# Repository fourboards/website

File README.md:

# fourboards
-----

Website based on the *Junior* theme designed and developed by [@jonobelotti_IO](https://twitter.com/jonobelotti_IO).

It is designed for [Jekyll](http://jekyllrb.com), the static site generator.

### Running 

`bundle exec jekyll serve`

## Credit

* [Pixyll theme](https://github.com/johnotander/pixyll) was used as a base for development of this theme.
* [Junior.IO's](http://www.junior.io/) website design served as inspiration for this theme's look.

## License

Open sourced under the [MIT license](LICENSE).

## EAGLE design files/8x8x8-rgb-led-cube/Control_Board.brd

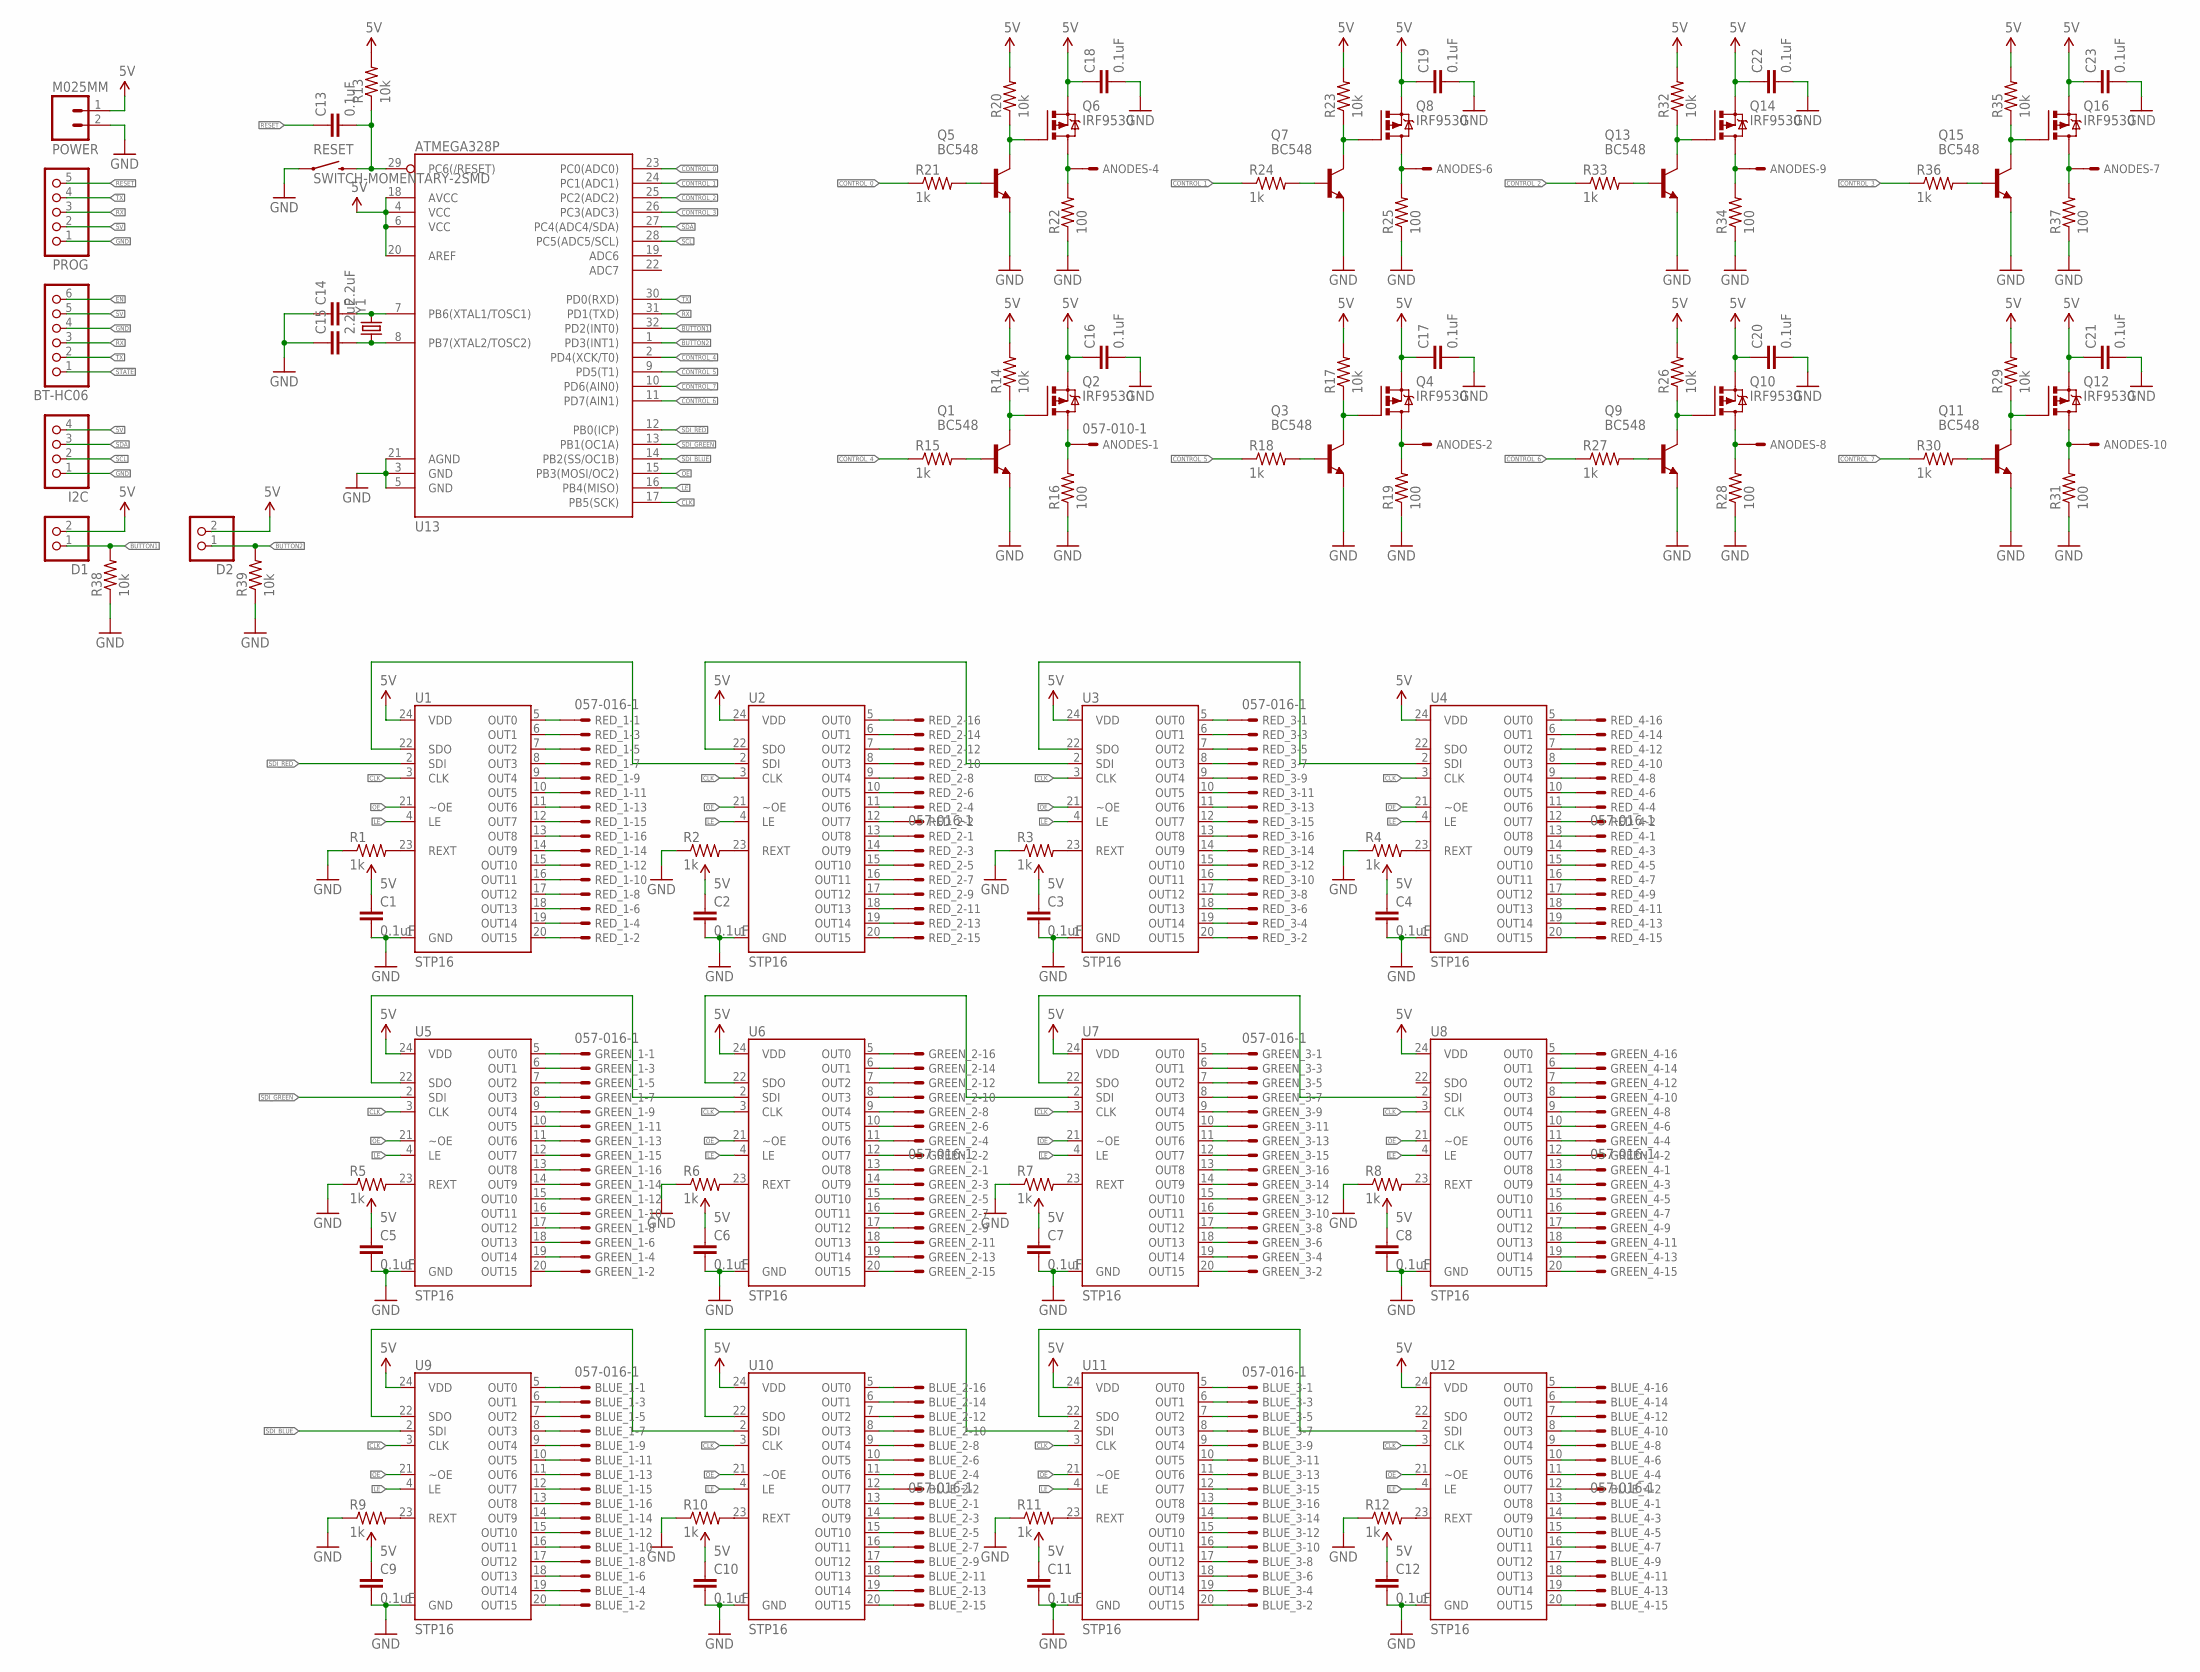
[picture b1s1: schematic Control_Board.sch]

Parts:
ANODES: 057-010-1
BLUE_1, BLUE_2, BLUE_3, BLUE_4: 057-016-1
BT-HC06: PINHD-1X6/90; 1X06/90
C1, C2, C3, C4, C5, C6, C7, C8, C9, C10, C11, C12, C13, C16, C17, C18, C19, C20, C21, C22, C23: 0.1uF; 0603-CAP
C14, C15: 2.2uF; 0603-CAP
D1, D2: PINHD-1X2/90; 1X02/90
GREEN_1, GREEN_2, GREEN_3, GREEN_4: 057-016-1
I2C: PINHD-1X4/90; 1X04/90
POWER: M025MM; SCREWTERMINAL-5MM-2
PROG: PINHD-1X5/90; 1X05/90
Q1, Q3, Q5, Q7, Q9, Q11, Q13, Q15: BC548; TO92-EBC
Q2, Q4, Q6, Q8, Q10, Q12, Q14, Q16: IRF9530; TO220BV
R1, R2, R3, R4, R5, R6, R7, R8, R9, R10, R11, R12, R15, R18, R21, R24, R27, R30, R33, R36: 1k; 0603-RES
R13, R14, R17, R20, R23, R26, R29, R32, R35, R38, R39: 10k; 0603-RES
R16, R19, R22, R25, R28, R31, R34, R37: 100; 0603-RES
RED_1, RED_2, RED_3, RED_4: 057-016-1
RESET: SWITCH-MOMENTARY-2SMD; TACTILE_SWITCH_SMD
U1, U2, U3, U4, U5, U6, U7, U8, U9, U10, U11, U12: STP16; TSSOP-24
U13: ATMEGA328P; TQFP32-08
Y1: CRYSTALHC49UV; HC49U-V

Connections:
5V: BT-HC06.5, C1.1, C2.1, C3.1, C4.1, C5.1, C6.1, C7.1, C8.1, C9.1, C10.1, C11.1, C12.1, C16.1, C17.1, C18.1, C19.1, C20.1, C21.1, C22.1, C23.1, D1.2, D2.2, I2C.4, POWER.1, PROG.2, Q2.S, Q4.S, Q6.S, Q8.S, Q10.S, Q12.S, Q14.S, Q16.S, R13.2, R14.2, R17.2, R20.2, R23.2, R26.2, R29.2, R32.2, R35.2, U1.24 (VDD), U2.24 (VDD), U3.24 (VDD), U4.24 (VDD), U5.24 (VDD), U6.24 (VDD), U7.24 (VDD), U8.24 (VDD), U9.24 (VDD), U10.24 (VDD), U11.24 (VDD), U12.24 (VDD), U13.6 (VCC), U13.18 (AVCC), U13.20 (AREF)
BUTTON1: D1.1, R38.2, U13.32 (PD2(INT0))
BUTTON2: D2.1, R39.2, U13.1 (PD3(INT1))
CLK: U1.3 (CLK), U2.3 (CLK), U3.3 (CLK), U4.3 (CLK), U5.3 (CLK), U6.3 (CLK), U7.3 (CLK), U8.3 (CLK), U9.3 (CLK), U10.3 (CLK), U11.3 (CLK), U12.3 (CLK), U13.17 (PB5(SCK))
CONTROL_0: R21.1, U13.23 (PC0(ADC0))
CONTROL_1: R24.1, U13.24 (PC1(ADC1))
CONTROL_2: R33.1, U13.25 (PC2(ADC2))
CONTROL_3: R36.1, U13.26 (PC3(ADC3))
CONTROL_4: R15.1, U13.2 (PD4(XCK/T0))
CONTROL_5: R18.1, U13.9 (PD5(T1))
CONTROL_6: R27.1, U13.11 (PD7(AIN1))
CONTROL_7: R30.1, U13.10 (PD6(AIN0))
EN: BT-HC06.6
GND: BT-HC06.4, C1.2, C2.2, C3.2, C4.2, C5.2, C6.2, C7.2, C8.2, C9.2, C10.2, C11.2, C12.2, C14.1, C15.1, C16.2, C17.2, C18.2, C19.2, C20.2, C21.2, C22.2, C23.2, I2C.1, POWER.2, PROG.1, Q1.E, Q3.E, Q5.E, Q7.E, Q9.E, Q11.E, Q13.E, Q15.E, R1.1, R2.1, R3.1, R4.1, R5.1, R6.1, R7.1, R8.1, R9.1, R10.1, R11.1, R12.1, R16.1, R19.1, R22.1, R25.1, R28.1, R31.1, R34.1, R37.1, R38.1, R39.1, RESET.1, U1.1 (GND), U2.1 (GND), U3.1 (GND), U4.1 (GND), U5.1 (GND), U6.1 (GND), U7.1 (GND), U8.1 (GND), U9.1 (GND), U10.1 (GND), U11.1 (GND), U12.1 (GND), U13.5 (GND), U13.21 (AGND)
LE: U1.4 (LE), U2.4 (LE), U3.4 (LE), U4.4 (LE), U5.4 (LE), U6.4 (LE), U7.4 (LE), U8.4 (LE), U9.4 (LE), U10.4 (LE), U11.4 (LE), U12.4 (LE), U13.16 (PB4(MISO))
LEVEL_0: ANODES.4, Q6.D, R22.2
LEVEL_1: ANODES.6, Q8.D, R25.2
LEVEL_2: ANODES.9, Q14.D, R34.2
LEVEL_3: ANODES.7, Q16.D, R37.2
LEVEL_4: ANODES.1, Q2.D, R16.2
LEVEL_5: ANODES.2, Q4.D, R19.2
LEVEL_6: ANODES.8, Q10.D, R28.2
LEVEL_7: ANODES.10, Q12.D, R31.2
unnamed: R1.2, U1.23 (REXT)
unnamed: RED_1.16, U1.13 (OUT8)
unnamed: RED_1.14, U1.14 (OUT9)
unnamed: RED_1.12, U1.15 (OUT10)
unnamed: RED_1.10, U1.16 (OUT11)
unnamed: RED_1.8, U1.17 (OUT12)
unnamed: RED_1.6, U1.18 (OUT13)
unnamed: RED_1.4, U1.19 (OUT14)
unnamed: RED_1.2, U1.20 (OUT15)
unnamed: RED_1.15, U1.12 (OUT7)
unnamed: RED_1.13, U1.11 (OUT6)
unnamed: RED_1.11, U1.10 (OUT5)
unnamed: RED_1.9, U1.9 (OUT4)
unnamed: RED_1.7, U1.8 (OUT3)
unnamed: RED_1.5, U1.7 (OUT2)
unnamed: RED_1.3, U1.6 (OUT1)
unnamed: RED_1.1, U1.5 (OUT0)
unnamed: R2.2, U2.23 (REXT)
unnamed: RED_2.2, U2.12 (OUT7)
unnamed: RED_2.4, U2.11 (OUT6)
unnamed: RED_2.6, U2.10 (OUT5)
unnamed: RED_2.8, U2.9 (OUT4)
unnamed: RED_2.10, U2.8 (OUT3)
unnamed: RED_2.12, U2.7 (OUT2)
unnamed: RED_2.14, U2.6 (OUT1)
unnamed: RED_2.16, U2.5 (OUT0)
unnamed: RED_2.1, U2.13 (OUT8)
unnamed: RED_2.3, U2.14 (OUT9)
unnamed: RED_2.5, U2.15 (OUT10)
unnamed: RED_2.7, U2.16 (OUT11)
unnamed: RED_2.9, U2.17 (OUT12)
unnamed: RED_2.11, U2.18 (OUT13)
unnamed: RED_2.13, U2.19 (OUT14)
unnamed: RED_2.15, U2.20 (OUT15)
unnamed: R3.2, U3.23 (REXT)
unnamed: RED_3.1, U3.5 (OUT0)
unnamed: RED_3.2, U3.20 (OUT15)
unnamed: RED_3.3, U3.6 (OUT1)
unnamed: RED_3.4, U3.19 (OUT14)
unnamed: RED_3.5, U3.7 (OUT2)
unnamed: RED_3.6, U3.18 (OUT13)
unnamed: RED_3.7, U3.8 (OUT3)
unnamed: RED_3.8, U3.17 (OUT12)
unnamed: RED_3.9, U3.9 (OUT4)
unnamed: RED_3.10, U3.16 (OUT11)
unnamed: RED_3.11, U3.10 (OUT5)
unnamed: RED_3.12, U3.15 (OUT10)
unnamed: RED_3.13, U3.11 (OUT6)
unnamed: RED_3.14, U3.14 (OUT9)
unnamed: RED_3.15, U3.12 (OUT7)
unnamed: RED_3.16, U3.13 (OUT8)
unnamed: R4.2, U4.23 (REXT)
unnamed: RED_4.1, U4.13 (OUT8)
unnamed: RED_4.2, U4.12 (OUT7)
unnamed: RED_4.3, U4.14 (OUT9)
unnamed: RED_4.4, U4.11 (OUT6)
unnamed: RED_4.5, U4.15 (OUT10)
unnamed: RED_4.6, U4.10 (OUT5)
unnamed: RED_4.7, U4.16 (OUT11)
unnamed: RED_4.8, U4.9 (OUT4)
unnamed: RED_4.9, U4.17 (OUT12)
unnamed: RED_4.10, U4.8 (OUT3)
unnamed: RED_4.11, U4.18 (OUT13)
unnamed: RED_4.12, U4.7 (OUT2)
unnamed: RED_4.13, U4.19 (OUT14)
unnamed: RED_4.14, U4.6 (OUT1)
unnamed: RED_4.15, U4.20 (OUT15)
unnamed: RED_4.16, U4.5 (OUT0)
unnamed: U1.22 (SDO), U2.2 (SDI)
unnamed: U2.22 (SDO), U3.2 (SDI)
unnamed: U3.22 (SDO), U4.2 (SDI)
unnamed: R5.2, U5.23 (REXT)
unnamed: R6.2, U6.23 (REXT)
unnamed: R7.2, U7.23 (REXT)
unnamed: R8.2, U8.23 (REXT)
unnamed: U5.22 (SDO), U6.2 (SDI)
unnamed: U6.22 (SDO), U7.2 (SDI)
unnamed: U7.22 (SDO), U8.2 (SDI)
unnamed: GREEN_1.16, U5.13 (OUT8)
unnamed: GREEN_1.14, U5.14 (OUT9)
unnamed: GREEN_1.12, U5.15 (OUT10)
unnamed: GREEN_1.10, U5.16 (OUT11)
unnamed: GREEN_1.8, U5.17 (OUT12)
unnamed: GREEN_1.6, U5.18 (OUT13)
unnamed: GREEN_1.4, U5.19 (OUT14)
unnamed: GREEN_1.2, U5.20 (OUT15)
unnamed: GREEN_1.15, U5.12 (OUT7)
unnamed: GREEN_1.13, U5.11 (OUT6)
unnamed: GREEN_1.11, U5.10 (OUT5)
unnamed: GREEN_1.9, U5.9 (OUT4)
unnamed: GREEN_1.7, U5.8 (OUT3)
unnamed: GREEN_1.5, U5.7 (OUT2)
unnamed: GREEN_1.3, U5.6 (OUT1)
unnamed: GREEN_1.1, U5.5 (OUT0)
unnamed: GREEN_3.1, U7.5 (OUT0)
unnamed: GREEN_3.2, U7.20 (OUT15)
unnamed: GREEN_3.3, U7.6 (OUT1)
unnamed: GREEN_3.4, U7.19 (OUT14)
unnamed: GREEN_3.5, U7.7 (OUT2)
unnamed: GREEN_3.6, U7.18 (OUT13)
unnamed: GREEN_3.7, U7.8 (OUT3)
unnamed: GREEN_3.8, U7.17 (OUT12)
unnamed: GREEN_3.9, U7.9 (OUT4)
unnamed: GREEN_3.10, U7.16 (OUT11)
unnamed: GREEN_3.11, U7.10 (OUT5)
unnamed: GREEN_3.12, U7.15 (OUT10)
unnamed: GREEN_3.13, U7.11 (OUT6)
unnamed: GREEN_3.14, U7.14 (OUT9)
unnamed: GREEN_3.15, U7.12 (OUT7)
unnamed: GREEN_3.16, U7.13 (OUT8)
unnamed: GREEN_2.2, U6.12 (OUT7)
unnamed: GREEN_2.4, U6.11 (OUT6)
unnamed: GREEN_2.6, U6.10 (OUT5)
unnamed: GREEN_2.8, U6.9 (OUT4)
unnamed: GREEN_2.10, U6.8 (OUT3)
unnamed: GREEN_2.12, U6.7 (OUT2)
unnamed: GREEN_2.14, U6.6 (OUT1)
unnamed: GREEN_2.16, U6.5 (OUT0)
unnamed: GREEN_2.1, U6.13 (OUT8)
unnamed: GREEN_2.3, U6.14 (OUT9)
unnamed: GREEN_2.5, U6.15 (OUT10)
unnamed: GREEN_2.7, U6.16 (OUT11)
unnamed: GREEN_2.9, U6.17 (OUT12)
unnamed: GREEN_2.11, U6.18 (OUT13)
unnamed: GREEN_2.13, U6.19 (OUT14)
unnamed: GREEN_2.15, U6.20 (OUT15)
unnamed: GREEN_4.1, U8.13 (OUT8)
unnamed: GREEN_4.2, U8.12 (OUT7)
unnamed: GREEN_4.3, U8.14 (OUT9)
unnamed: GREEN_4.4, U8.11 (OUT6)
unnamed: GREEN_4.5, U8.15 (OUT10)
unnamed: GREEN_4.6, U8.10 (OUT5)
unnamed: GREEN_4.7, U8.16 (OUT11)
unnamed: GREEN_4.8, U8.9 (OUT4)
unnamed: GREEN_4.9, U8.17 (OUT12)
unnamed: GREEN_4.10, U8.8 (OUT3)
unnamed: GREEN_4.11, U8.18 (OUT13)
unnamed: GREEN_4.12, U8.7 (OUT2)
unnamed: GREEN_4.13, U8.19 (OUT14)
unnamed: GREEN_4.14, U8.6 (OUT1)
unnamed: GREEN_4.15, U8.20 (OUT15)
unnamed: GREEN_4.16, U8.5 (OUT0)
unnamed: R9.2, U9.23 (REXT)
unnamed: R10.2, U10.23 (REXT)
unnamed: R11.2, U11.23 (REXT)
unnamed: R12.2, U12.23 (REXT)
unnamed: U9.22 (SDO), U10.2 (SDI)
unnamed: U10.22 (SDO), U11.2 (SDI)
unnamed: U11.22 (SDO), U12.2 (SDI)
unnamed: BLUE_1.16, U9.13 (OUT8)
unnamed: BLUE_1.14, U9.14 (OUT9)
unnamed: BLUE_1.12, U9.15 (OUT10)
unnamed: BLUE_1.10, U9.16 (OUT11)
unnamed: BLUE_1.8, U9.17 (OUT12)
unnamed: BLUE_1.6, U9.18 (OUT13)
unnamed: BLUE_1.4, U9.19 (OUT14)
unnamed: BLUE_1.2, U9.20 (OUT15)
unnamed: BLUE_1.15, U9.12 (OUT7)
unnamed: BLUE_1.13, U9.11 (OUT6)
unnamed: BLUE_1.11, U9.10 (OUT5)
unnamed: BLUE_1.9, U9.9 (OUT4)
unnamed: BLUE_1.7, U9.8 (OUT3)
unnamed: BLUE_1.5, U9.7 (OUT2)
unnamed: BLUE_1.3, U9.6 (OUT1)
unnamed: BLUE_1.1, U9.5 (OUT0)
unnamed: BLUE_3.1, U11.5 (OUT0)
unnamed: BLUE_3.2, U11.20 (OUT15)
unnamed: BLUE_3.3, U11.6 (OUT1)
unnamed: BLUE_3.4, U11.19 (OUT14)
unnamed: BLUE_3.5, U11.7 (OUT2)
unnamed: BLUE_3.6, U11.18 (OUT13)
unnamed: BLUE_3.7, U11.8 (OUT3)
unnamed: BLUE_3.8, U11.17 (OUT12)
unnamed: BLUE_3.9, U11.9 (OUT4)
unnamed: BLUE_3.10, U11.16 (OUT11)
unnamed: BLUE_3.11, U11.10 (OUT5)
unnamed: BLUE_3.12, U11.15 (OUT10)
unnamed: BLUE_3.13, U11.11 (OUT6)
unnamed: BLUE_3.14, U11.14 (OUT9)
unnamed: BLUE_3.15, U11.12 (OUT7)
unnamed: BLUE_3.16, U11.13 (OUT8)
unnamed: BLUE_2.2, U10.12 (OUT7)
unnamed: BLUE_2.4, U10.11 (OUT6)
unnamed: BLUE_2.6, U10.10 (OUT5)
unnamed: BLUE_2.8, U10.9 (OUT4)
unnamed: BLUE_2.10, U10.8 (OUT3)
unnamed: BLUE_2.12, U10.7 (OUT2)
unnamed: BLUE_2.14, U10.6 (OUT1)
unnamed: BLUE_2.16, U10.5 (OUT0)
unnamed: BLUE_2.1, U10.13 (OUT8)
unnamed: BLUE_2.3, U10.14 (OUT9)
unnamed: BLUE_2.5, U10.15 (OUT10)
unnamed: BLUE_2.7, U10.16 (OUT11)
unnamed: BLUE_2.9, U10.17 (OUT12)
unnamed: BLUE_2.11, U10.18 (OUT13)
unnamed: BLUE_2.13, U10.19 (OUT14)
unnamed: BLUE_2.15, U10.20 (OUT15)
unnamed: BLUE_4.1, U12.13 (OUT8)
unnamed: BLUE_4.2, U12.12 (OUT7)
unnamed: BLUE_4.3, U12.14 (OUT9)
unnamed: BLUE_4.4, U12.11 (OUT6)
unnamed: BLUE_4.5, U12.15 (OUT10)
unnamed: BLUE_4.6, U12.10 (OUT5)
unnamed: BLUE_4.7, U12.16 (OUT11)
unnamed: BLUE_4.8, U12.9 (OUT4)
unnamed: BLUE_4.9, U12.17 (OUT12)
unnamed: BLUE_4.10, U12.8 (OUT3)
unnamed: BLUE_4.11, U12.18 (OUT13)
unnamed: BLUE_4.12, U12.7 (OUT2)
unnamed: BLUE_4.13, U12.19 (OUT14)
unnamed: BLUE_4.14, U12.6 (OUT1)
unnamed: BLUE_4.15, U12.20 (OUT15)
unnamed: BLUE_4.16, U12.5 (OUT0)
unnamed: C13.2, R13.1, RESET.3 (2), U13.29 (PC6(/RESET))
unnamed: Q1.C, Q2.G, R14.1
unnamed: C14.2, U13.7 (PB6(XTAL1/TOSC1)), Y1.2
unnamed: C15.2, U13.8 (PB7(XTAL2/TOSC2)), Y1.1
unnamed: Q1.B, R15.2
unnamed: Q3.C, Q4.G, R17.1
unnamed: Q3.B, R18.2
unnamed: Q5.C, Q6.G, R20.1
unnamed: Q5.B, R21.2
unnamed: Q7.C, Q8.G, R23.1
unnamed: Q7.B, R24.2
unnamed: Q9.C, Q10.G, R26.1
unnamed: Q9.B, R27.2
unnamed: Q11.C, Q12.G, R29.1
unnamed: Q11.B, R30.2
unnamed: Q13.C, Q14.G, R32.1
unnamed: Q13.B, R33.2
unnamed: Q15.C, Q16.G, R35.1
unnamed: Q15.B, R36.2
OE: U1.21 (~OE), U2.21 (~OE), U3.21 (~OE), U4.21 (~OE), U5.21 (~OE), U6.21 (~OE), U7.21 (~OE), U8.21 (~OE), U9.21 (~OE), U10.21 (~OE), U11.21 (~OE), U12.21 (~OE), U13.15 (PB3(MOSI/OC2))
RESET: C13.1, PROG.5
RX: BT-HC06.3, PROG.3, U13.31 (PD1(TXD))
SCL: I2C.2, U13.28 (PC5(ADC5/SCL))
SDA: I2C.3, U13.27 (PC4(ADC4/SDA))
SDI_BLUE: U9.2 (SDI), U13.14 (PB2(SS/OC1B))
SDI_GREEN: U5.2 (SDI), U13.13 (PB1(OC1A))
SDI_RED: U1.2 (SDI), U13.12 (PB0(ICP))
STATE: BT-HC06.1
TX: BT-HC06.2, PROG.4, U13.30 (PD0(RXD))

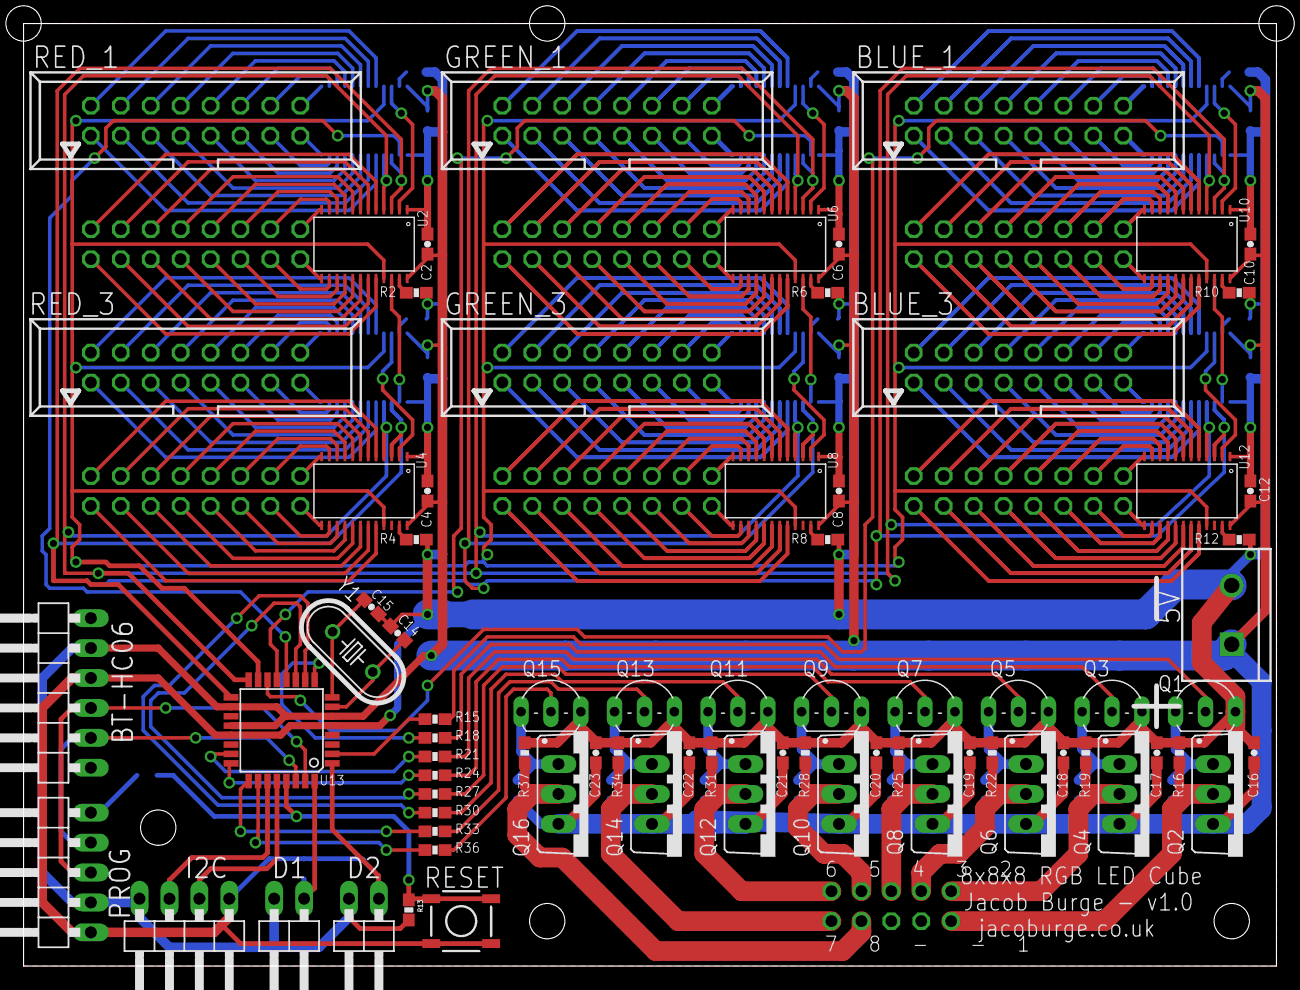
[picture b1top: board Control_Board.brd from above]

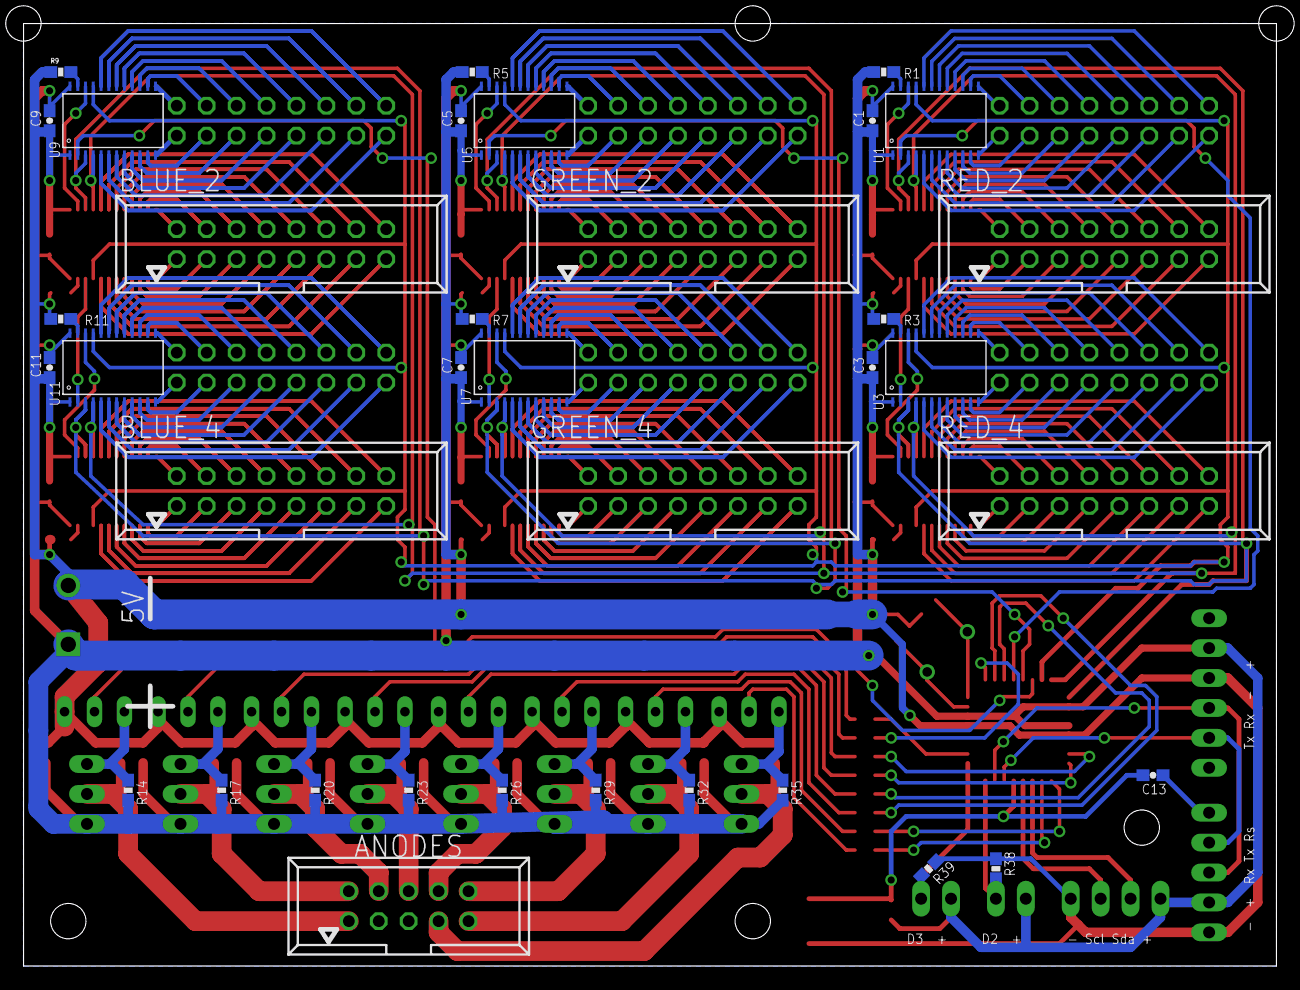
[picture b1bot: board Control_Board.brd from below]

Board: 2 copper layers, 106.4 x 80.0 mm, 112 parts (36 on the bottom side), 263 nets.

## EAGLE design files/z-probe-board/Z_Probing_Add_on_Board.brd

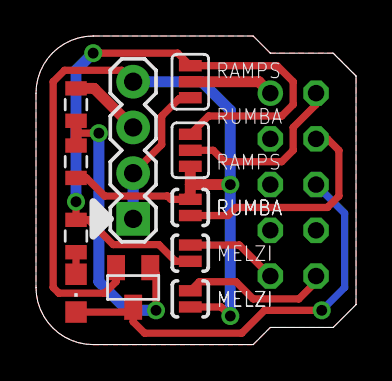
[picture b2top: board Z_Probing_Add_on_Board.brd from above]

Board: 2 copper layers, 17.8 x 17.1 mm, 12 parts (1 on the bottom side), 12 nets.

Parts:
LED1: CHIPLED_0805
MELZI_GND, MELZI_GND1: SOLDERJUMPERNO; SJ_2S-NO
Q1: BSS138; SOT23
R1: 150R; 0805
R2: 10K; 0805
R3: 1K; 0805
RUMBA_GND: SOLDERJUMPERNO; SJ_2S-NO
SENSOR: 1X04
SJ1, SJ2: SJ_3
SV1: FE05-2

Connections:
2.8V: SENSOR.1, SENSOR.2, SJ2.3
5V: MELZI_GND1.1, R1.2, SJ1.1, SJ2.1
GND: MELZI_GND.2, Q1.2, R2.1, RUMBA_GND.2, SENSOR.4, SJ1.3
unnamed: RUMBA_GND.1, SV1.4
unnamed: MELZI_GND.1, SV1.10
unnamed: SJ1.2, SV1.2
unnamed: R3.2, SENSOR.3
unnamed: SJ2.2, SV1.1
unnamed: Q1.1, R2.2, R3.1
unnamed: MELZI_GND1.2, SV1.9
unnamed: LED1.A, R1.1
SIGNAL: LED1.C, Q1.3, SV1.8

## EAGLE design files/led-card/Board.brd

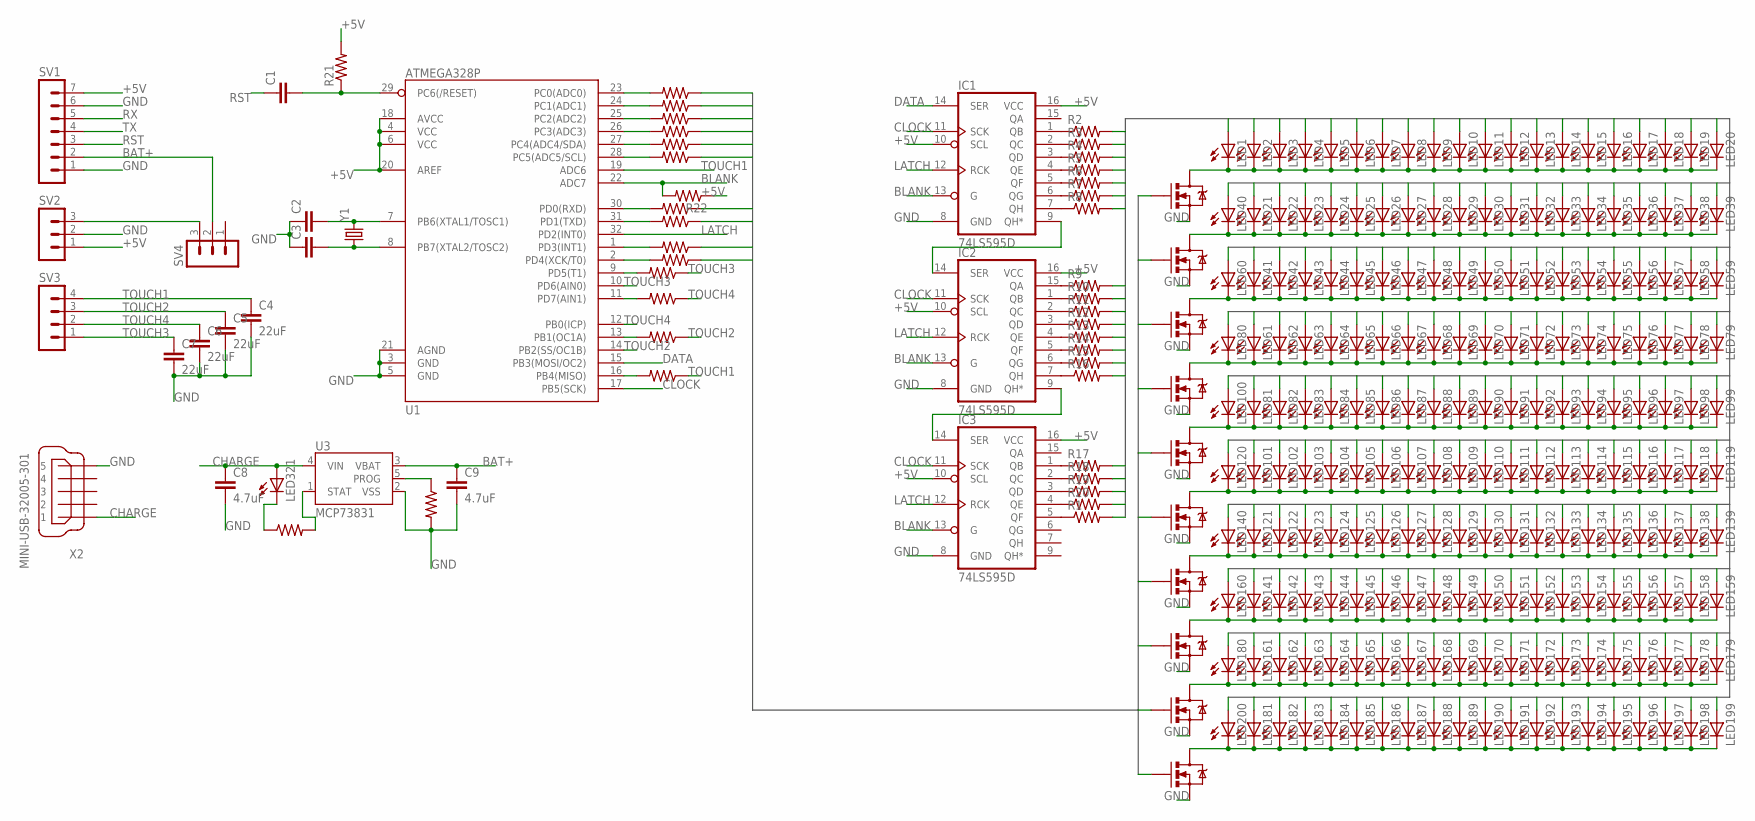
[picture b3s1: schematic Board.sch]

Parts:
2K: 2K; 0603-RES
470R: 470R; 0603-RES
C1: CAPPTH1; CAP-PTH-5MM
C2, C3, C4, C5, C6, C7: 22uF; 0805
C8, C9: 4.7uF; 0603-CAP
IC1, IC2, IC3: 74LS595D; SO16
LED1, LED2, LED3, LED4, LED5, LED6, LED7, LED8, LED9, LED10, LED11, LED12, LED13, LED14, LED15, LED16, LED17, LED18, LED19, LED20, LED21, LED22, LED23, LED24, LED25, LED26, LED27, LED28, LED29, LED30, LED31, LED32, LED33, LED34, LED35, LED36, LED37, LED38, LED39, LED40, LED41, LED42, LED43, LED44, LED45, LED46, LED47, LED48, LED49, LED50, LED51, LED52, LED53, LED54, LED55, LED56, LED57, LED58, LED59, LED60, LED61, LED62, LED63, LED64, LED65, LED66, LED67, LED68, LED69, LED70, LED71, LED72, LED73, LED74, LED75, LED76, LED77, LED78, LED79, LED80, LED81, LED82, LED83, LED84, LED85, LED86, LED87, LED88, LED89, LED90, LED91, LED92, LED93, LED94, LED95, LED96, LED97, LED98, LED99, LED100, LED101, LED102, LED103, LED104, LED105, LED106, LED107, LED108, LED109, LED110, LED111, LED112, LED113, LED114, LED115, LED116, LED117, LED118, LED119, LED120, LED121, LED122, LED123, LED124, LED125, LED126, LED127, LED128, LED129, LED130, LED131, LED132, LED133, LED134, LED135, LED136, LED137, LED138, LED139, LED140, LED141, LED142, LED143, LED144, LED145, LED146, LED147, LED148, LED149, LED150, LED151, LED152, LED153, LED154, LED155, LED156, LED157, LED158, LED159, LED160, LED161, LED162, LED163, LED164, LED165, LED166, LED167, LED168, LED169, LED170, LED171, LED172, LED173, LED174, LED175, LED176, LED177, LED178, LED179, LED180, LED181, LED182, LED183, LED184, LED185, LED186, LED187, LED188, LED189, LED190, LED191, LED192, LED193, LED194, LED195, LED196, LED197, LED198, LED199, LED200, LED321: LED0603; LED-0603
Q1, Q2, Q3, Q6, Q8, Q10, Q12, Q14, Q16, Q19: MOSFET-NCHANNELBSS123LT1G; SOT23
R1, R2, R3, R4, R5, R6, R7, R8, R9, R10, R11, R12, R13, R14, R15, R16, R17, R18, R19, R20, R30, R31, R32, R33, R34, R35, R36, R37, R38, R39: 100; 0603-RES
R21, R22: 10K; 0603-RES
R23, R24, R26, R40: 1M; 0603-RES
SV1: MA07-1
SV2, SV4: MA03-1
SV3: MA04-1
U1: ATMEGA328P; TQFP32-08
U3: MCP73831; SOT23-5
X2: MINI-USB-32005-301; 32005-301
Y1: CRYSTAL5X3; CRYSTAL-SMD-5X3

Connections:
+5V: IC1.10 (SCL), IC1.16 (VCC), IC2.10 (SCL), IC2.16 (VCC), IC3.10 (SCL), IC3.16 (VCC), R21.2, R22.1, SV1.7, SV2.1, U1.4 (VCC), U1.6 (VCC), U1.18 (AVCC), U1.20 (AREF)
A0: Q1.1 (G), R37.1
A1: Q2.1 (G), R36.1
A2: Q3.1 (G), R39.1
A3: Q6.1 (G), R38.1
A4: Q8.1 (G), R35.1
A5: Q10.1 (G), R34.1
A6: Q12.1 (G), R33.1
A7: Q14.1 (G), R32.1
A8: Q16.1 (G), R31.1
A9: Q19.1 (G), R30.1
BAT+: C9.1, SV1.2, SV4.2, U3.3 (VBAT)
BLANK: IC1.13 (G), IC2.13 (G), IC3.13 (G), R22.2, U1.22 (ADC7)
CHARGE: C8.1, LED321.A, U3.4 (VIN), X2.1
CLOCK: IC1.11 (SCK), IC2.11 (SCK), IC3.11 (SCK), U1.17 (PB5(SCK))
D0: LED20.A, LED40.A, LED60.A, LED80.A, LED100.A, LED120.A, LED140.A, LED160.A, LED180.A, LED200.A, R1.2
D1: LED2.A, LED21.A, LED41.A, LED61.A, LED81.A, LED101.A, LED121.A, LED141.A, LED161.A, LED181.A, R2.2
D2: LED3.A, LED22.A, LED42.A, LED62.A, LED82.A, LED102.A, LED122.A, LED142.A, LED162.A, LED182.A, R3.2
D3: LED4.A, LED23.A, LED43.A, LED63.A, LED83.A, LED103.A, LED123.A, LED143.A, LED163.A, LED183.A, R4.2
D4: LED5.A, LED24.A, LED44.A, LED64.A, LED84.A, LED104.A, LED124.A, LED144.A, LED164.A, LED184.A, R5.2
D5: LED6.A, LED25.A, LED45.A, LED65.A, LED85.A, LED105.A, LED125.A, LED145.A, LED165.A, LED185.A, R6.2
D6: LED7.A, LED26.A, LED46.A, LED66.A, LED86.A, LED106.A, LED126.A, LED146.A, LED166.A, LED186.A, R7.2
D7: LED8.A, LED27.A, LED47.A, LED67.A, LED87.A, LED107.A, LED127.A, LED147.A, LED167.A, LED187.A, R8.2
D8: LED9.A, LED28.A, LED48.A, LED68.A, LED88.A, LED108.A, LED128.A, LED148.A, LED168.A, LED188.A, R9.2
D9: LED10.A, LED29.A, LED49.A, LED69.A, LED89.A, LED109.A, LED129.A, LED149.A, LED169.A, LED189.A, R10.2
D10: LED11.A, LED30.A, LED50.A, LED70.A, LED90.A, LED110.A, LED130.A, LED150.A, LED170.A, LED190.A, R11.2
D11: LED12.A, LED31.A, LED51.A, LED71.A, LED91.A, LED111.A, LED131.A, LED151.A, LED171.A, LED191.A, R12.2
D12: LED13.A, LED32.A, LED52.A, LED72.A, LED92.A, LED112.A, LED132.A, LED152.A, LED172.A, LED192.A, R13.2
D13: LED14.A, LED33.A, LED53.A, LED73.A, LED93.A, LED113.A, LED133.A, LED153.A, LED173.A, LED193.A, R14.2
D14: LED15.A, LED34.A, LED54.A, LED74.A, LED94.A, LED114.A, LED134.A, LED154.A, LED174.A, LED194.A, R15.2
D15: LED16.A, LED35.A, LED55.A, LED75.A, LED95.A, LED115.A, LED135.A, LED155.A, LED175.A, LED195.A, R16.2
D16: LED17.A, LED36.A, LED56.A, LED76.A, LED96.A, LED116.A, LED136.A, LED156.A, LED176.A, LED196.A, R17.2
D17: LED18.A, LED37.A, LED57.A, LED77.A, LED97.A, LED117.A, LED137.A, LED157.A, LED177.A, LED197.A, R18.2
D18: LED19.A, LED38.A, LED58.A, LED78.A, LED98.A, LED118.A, LED138.A, LED158.A, LED178.A, LED198.A, R19.2
D19: LED1.A, LED39.A, LED59.A, LED79.A, LED99.A, LED119.A, LED139.A, LED159.A, LED179.A, LED199.A, R20.2
DATA: IC1.14 (SER), U1.15 (PB3(MOSI/OC2))
GND: 2K.2, C2.1, C3.1, C4.2, C5.2, C6.2, C7.2, C8.2, C9.2, IC1.8 (GND), IC2.8 (GND), IC3.8 (GND), Q1.2 (S), Q2.2 (S), Q3.2 (S), Q6.2 (S), Q8.2 (S), Q10.2 (S), Q12.2 (S), Q14.2 (S), Q16.2 (S), Q19.2 (S), SV1.1, SV1.6, SV2.2, U1.3 (GND), U1.5 (GND), U1.21 (AGND), U3.2 (VSS), X2.5
LATCH: IC1.12 (RCK), IC2.12 (RCK), IC3.12 (RCK), U1.32 (PD2(INT0))
unnamed: LED1.C, LED2.C, LED3.C, LED4.C, LED5.C, LED6.C, LED7.C, LED8.C, LED9.C, LED10.C, LED11.C, LED12.C, LED13.C, LED14.C, LED15.C, LED16.C, LED17.C, LED18.C, LED19.C, LED20.C, Q1.3 (D)
unnamed: LED21.C, LED22.C, LED23.C, LED24.C, LED25.C, LED26.C, LED27.C, LED28.C, LED29.C, LED30.C, LED31.C, LED32.C, LED33.C, LED34.C, LED35.C, LED36.C, LED37.C, LED38.C, LED39.C, LED40.C, Q2.3 (D)
unnamed: LED181.C, LED182.C, LED183.C, LED184.C, LED185.C, LED186.C, LED187.C, LED188.C, LED189.C, LED190.C, LED191.C, LED192.C, LED193.C, LED194.C, LED195.C, LED196.C, LED197.C, LED198.C, LED199.C, LED200.C, Q19.3 (D)
unnamed: LED41.C, LED42.C, LED43.C, LED44.C, LED45.C, LED46.C, LED47.C, LED48.C, LED49.C, LED50.C, LED51.C, LED52.C, LED53.C, LED54.C, LED55.C, LED56.C, LED57.C, LED58.C, LED59.C, LED60.C, Q3.3 (D)
unnamed: LED61.C, LED62.C, LED63.C, LED64.C, LED65.C, LED66.C, LED67.C, LED68.C, LED69.C, LED70.C, LED71.C, LED72.C, LED73.C, LED74.C, LED75.C, LED76.C, LED77.C, LED78.C, LED79.C, LED80.C, Q6.3 (D)
unnamed: LED81.C, LED82.C, LED83.C, LED84.C, LED85.C, LED86.C, LED87.C, LED88.C, LED89.C, LED90.C, LED91.C, LED92.C, LED93.C, LED94.C, LED95.C, LED96.C, LED97.C, LED98.C, LED99.C, LED100.C, Q8.3 (D)
unnamed: LED101.C, LED102.C, LED103.C, LED104.C, LED105.C, LED106.C, LED107.C, LED108.C, LED109.C, LED110.C, LED111.C, LED112.C, LED113.C, LED114.C, LED115.C, LED116.C, LED117.C, LED118.C, LED119.C, LED120.C, Q10.3 (D)
unnamed: LED121.C, LED122.C, LED123.C, LED124.C, LED125.C, LED126.C, LED127.C, LED128.C, LED129.C, LED130.C, LED131.C, LED132.C, LED133.C, LED134.C, LED135.C, LED136.C, LED137.C, LED138.C, LED139.C, LED140.C, Q12.3 (D)
unnamed: LED141.C, LED142.C, LED143.C, LED144.C, LED145.C, LED146.C, LED147.C, LED148.C, LED149.C, LED150.C, LED151.C, LED152.C, LED153.C, LED154.C, LED155.C, LED156.C, LED157.C, LED158.C, LED159.C, LED160.C, Q14.3 (D)
unnamed: LED161.C, LED162.C, LED163.C, LED164.C, LED165.C, LED166.C, LED167.C, LED168.C, LED169.C, LED170.C, LED171.C, LED172.C, LED173.C, LED174.C, LED175.C, LED176.C, LED177.C, LED178.C, LED179.C, LED180.C, Q16.3 (D)
unnamed: R30.2, U1.23 (PC0(ADC0))
unnamed: R31.2, U1.24 (PC1(ADC1))
unnamed: R32.2, U1.25 (PC2(ADC2))
unnamed: R33.2, U1.26 (PC3(ADC3))
unnamed: R34.2, U1.27 (PC4(ADC4/SDA))
unnamed: R35.2, U1.28 (PC5(ADC5/SCL))
unnamed: IC1.2 (QC), R3.1
unnamed: IC1.3 (QD), R4.1
unnamed: IC1.4 (QE), R5.1
unnamed: IC1.5 (QF), R6.1
unnamed: IC1.6 (QG), R7.1
unnamed: IC1.7 (QH), R8.1
unnamed: IC2.15 (QA), R9.1
unnamed: IC2.1 (QB), R10.1
unnamed: IC2.2 (QC), R11.1
unnamed: IC2.3 (QD), R12.1
unnamed: IC2.4 (QE), R13.1
unnamed: IC2.5 (QF), R14.1
unnamed: IC2.6 (QG), R15.1
unnamed: IC2.7 (QH), R16.1
unnamed: IC3.1 (QB), R17.1
unnamed: IC3.2 (QC), R18.1
unnamed: IC3.3 (QD), R19.1
unnamed: IC3.4 (QE), R20.1
unnamed: IC3.5 (QF), R1.1
unnamed: IC1.1 (QB), R2.1
unnamed: C2.2, U1.7 (PB6(XTAL1/TOSC1)), Y1.3 (2)
unnamed: C1.2, R21.1, U1.29 (PC6(/RESET))
unnamed: C3.2, U1.8 (PB7(XTAL2/TOSC2)), Y1.1
unnamed: SV2.3, SV4.3
unnamed: 470R.1, LED321.C
unnamed: 470R.2, U3.1 (STAT)
unnamed: R23.2, U1.9 (PD5(T1))
unnamed: R24.2, U1.13 (PB1(OC1A))
unnamed: 2K.1, U3.5 (PROG)
unnamed: IC1.9 (QH*), IC2.14 (SER)
unnamed: IC2.9 (QH*), IC3.14 (SER)
unnamed: R26.2, U1.16 (PB4(MISO))
unnamed: R40.2, U1.11 (PD7(AIN1))
unnamed: R36.2, U1.1 (PD3(INT1))
unnamed: R37.2, U1.2 (PD4(XCK/T0))
RST: C1.1, SV1.3
RX: R38.2, SV1.5, U1.30 (PD0(RXD))
TOUCH1: C4.1, R26.1, SV3.4, U1.19 (ADC6)
TOUCH2: C5.1, R24.1, SV3.3, U1.14 (PB2(SS/OC1B))
TOUCH3: C7.1, R23.1, SV3.1, U1.10 (PD6(AIN0))
TOUCH4: C6.1, R40.1, SV3.2, U1.12 (PB0(ICP))
TX: R39.2, SV1.4, U1.31 (PD1(TXD))

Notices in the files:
parts and their libraries:
SparkFun-Capacitors: Licensing: CC v3.0 Share-Alike You are welcome to use this library for commercial purposes.
SparkFun-Connectors: Licensing: Creative Commons ShareAlike 4.0 International - https://creativecommons.org/licenses/by-sa/4.0
